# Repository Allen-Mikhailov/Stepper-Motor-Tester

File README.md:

# Stepper-Coil-Tester (WIP)
The device will allow you to test the functionality of the drv8825 driver without any code

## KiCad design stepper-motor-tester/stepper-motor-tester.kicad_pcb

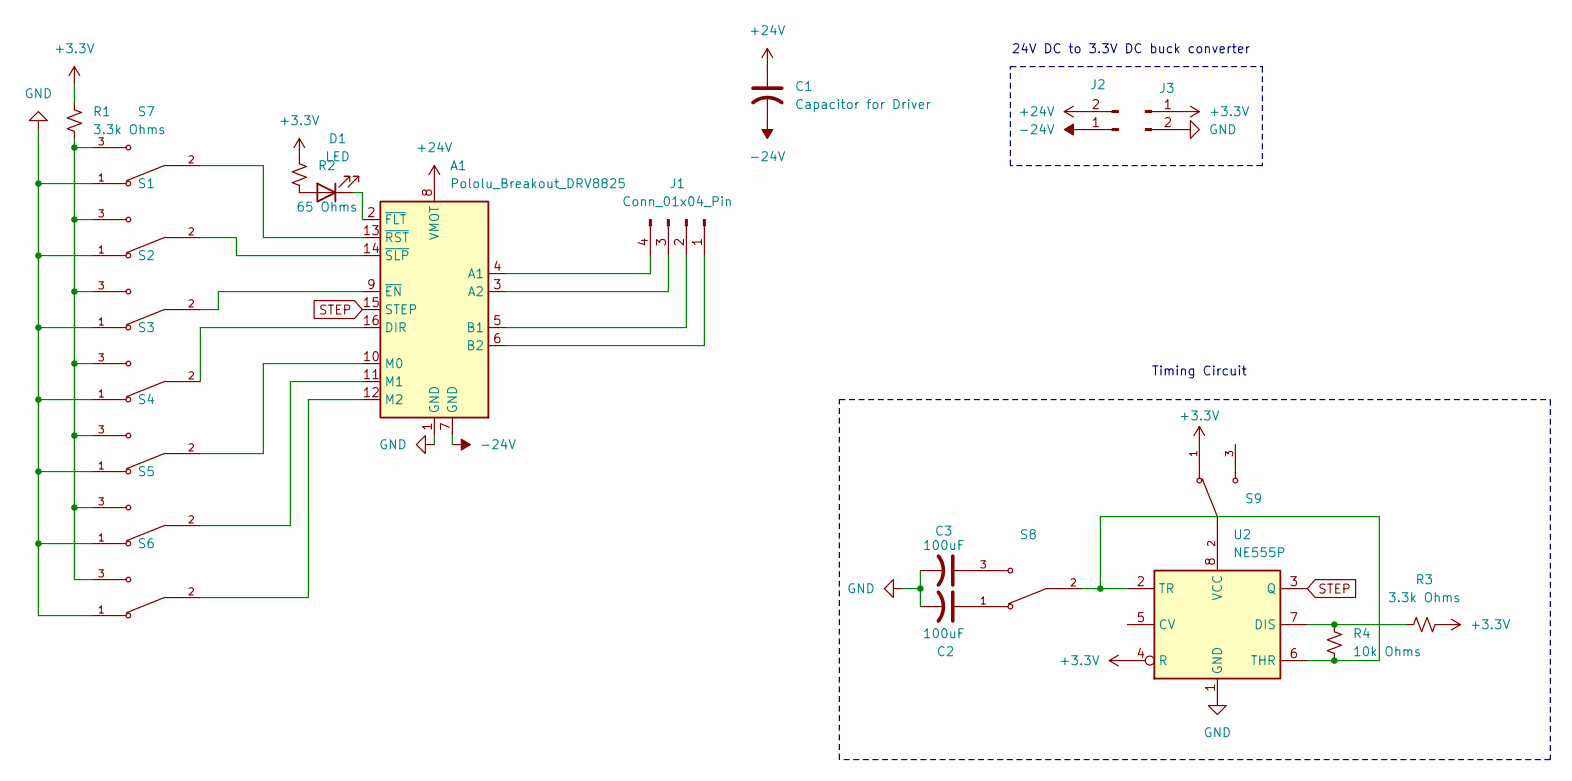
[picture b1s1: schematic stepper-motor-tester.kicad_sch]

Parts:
A1: Pololu_Breakout_DRV8825; Pololu_Breakout-16_15.2x20.3mm
C1: Capacitor for Driver; C_Radial_D6.3mm_H11.0mm_P2.50mm
C2, C3: 100uF; C_Radial_D6.3mm_H11.0mm_P2.50mm
D1: LED; LED_D3.0mm
J1: Conn_01x04_Pin; PinHeader_1x04_P2.54mm_Vertical
J2, J3: Conn_01x02_Pin; PinHeader_1x02_P2.54mm_Vertical
R1: 3.3k Ohms
R2: 65 Ohms; R_Axial_DIN0207_L6.3mm_D2.5mm_P10.16mm_Horizontal
R3: 3.3k Ohms; R_Axial_DIN0207_L6.3mm_D2.5mm_P10.16mm_Horizontal
R4: 10k Ohms; R_Axial_DIN0207_L6.3mm_D2.5mm_P10.16mm_Horizontal
S1, S2, S3, S4, S5, S6, S7, S8, S9: 500SSP1S1M2REA; SW_500SSP1S1M2REA
U2: NE555P; DIP-8_W7.62mm

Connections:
+3.3V: J3.1, R1.1, R2.1, R3.2, S9.1, U2.4 (R)
+24V: A1.8 (VMOT), C1.1, J2.2
-24V: A1.7 (GND), C1.2, J2.1
GND: A1.1 (GND), C2.2, C3.2, J3.2, S1.1, S2.1, S3.1, S4.1, S5.1, S6.1, S7.1, U2.1 (GND)
unnamed: A1.4 (A1), J1.4
unnamed: A1.3 (A2), J1.3
unnamed: A1.5 (B1), J1.2
unnamed: A1.6 (B2), J1.1
unnamed: A1.16 (DIR), S3.2
unnamed: A1.10 (M0), S4.2
unnamed: A1.11 (M1), S5.2
unnamed: A1.12 (M2), S6.2
unnamed: A1.9 (~EN), S2.2
unnamed: A1.2 (~FLT), D1.1 (K)
unnamed: A1.13 (~RST), S7.2
unnamed: A1.14 (~SLP), S1.2
unnamed: C2.1, S8.1
unnamed: C3.1, S8.3
unnamed: D1.2 (A), R2.2
unnamed: R1.2, S1.3, S2.3, S3.3, S4.3, S5.3, S6.3, S7.3
unnamed: R3.1, R4.2, U2.7 (DIS)
unnamed: R4.1, S8.2, U2.2 (TR), U2.6 (THR)
unnamed: S9.2, U2.8 (VCC)
STEP: A1.15 (STEP), U2.3 (Q)

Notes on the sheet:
24V DC to 3.3V DC buck converter
Timing Circuit

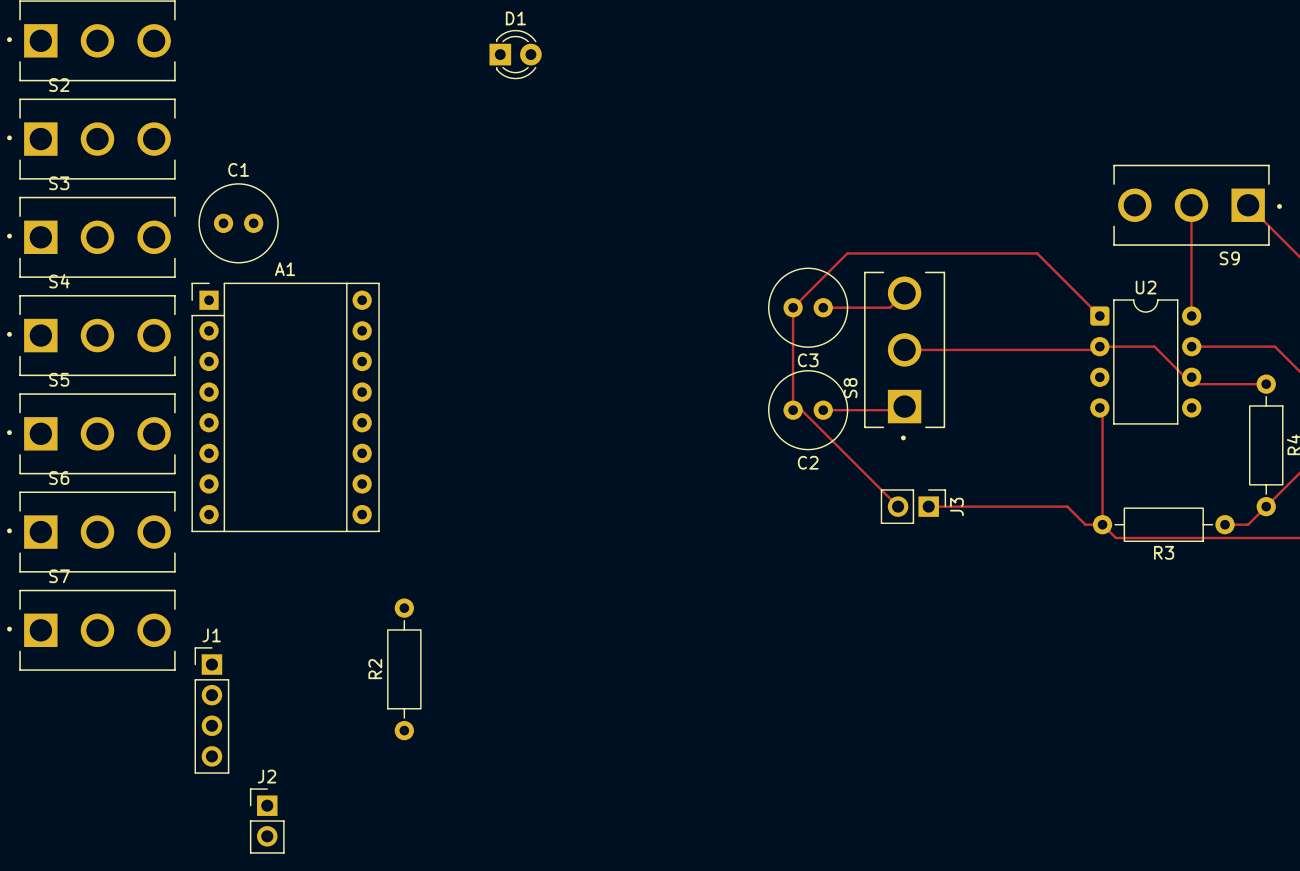
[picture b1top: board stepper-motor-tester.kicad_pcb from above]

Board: 2 copper layers, 21 parts (0 on the bottom side), 24 nets.

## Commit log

2025-07-27 Skematic Finished for Simple Tester, but PCB layout still in works
